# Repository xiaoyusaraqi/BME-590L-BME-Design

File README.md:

# BME-590L-BME-Design
# LED light that is button-activated to switch between the following operating modes:
  Off
  Brightest
  Intermediate Brightness
  Least Bright
  Flashing @ 2 Hz
# Self-contained device with LED and button exposed.
# Extra credit possibilities:
   Battery life indicator
   Waterproof enclosure
   You tell us!
# Constraints
   Run on single battery up to 9 V
   Electronics connected to a single PCB (can be single- or double-sided)
   Cannot weight more than 1 lb
   Cannot have a single dimension > 6 in
   Cannot cost more than $50 to duplicate unit
   Battery must be easily replaceable
# Evaluation

   Minimize weight
   Minimize size
   Maximize Brightest mode
   Minimize power draw / maximize battery life
   Survive 3 foot drop with battery installed
 # Create-and-maintain a GitHub project repository to maintain version history of:
  Mechanical CAD (PDFs + more)
  Electronic CAD (PDFs + more)
  Software
  Testing data
  Design history / notes
  Specification sheets
  Usage notes (README.md)
  Kanban board / Issues / Milestones

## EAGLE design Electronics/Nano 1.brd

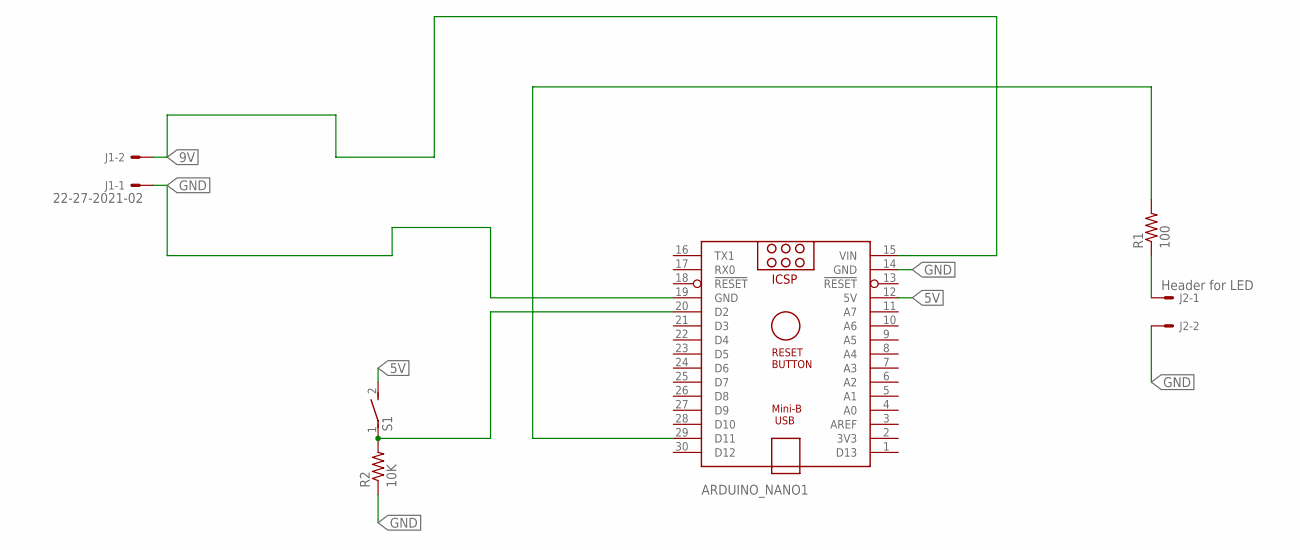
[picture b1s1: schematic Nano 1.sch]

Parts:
ARDUINO_NANO1: ARDUINO_NANO
J1: 22-27-2021-02; 6410-02
J2: Header for LED; 6410-02
R1: 100; 0207/12
R2: 10K; 0207/12
S1: DS01E; DS-01

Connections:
5V: ARDUINO_NANO1.12 (5V), S1.2
9V: ARDUINO_NANO1.15 (VIN), J1.2
+: J2.1, R1.1
GND: ARDUINO_NANO1.14 (GND), ARDUINO_NANO1.19 (GND), J1.1, J2.2, R2.1
unnamed: ARDUINO_NANO1.20 (D2), R2.2, S1.1
unnamed: ARDUINO_NANO1.29 (D11), R1.2

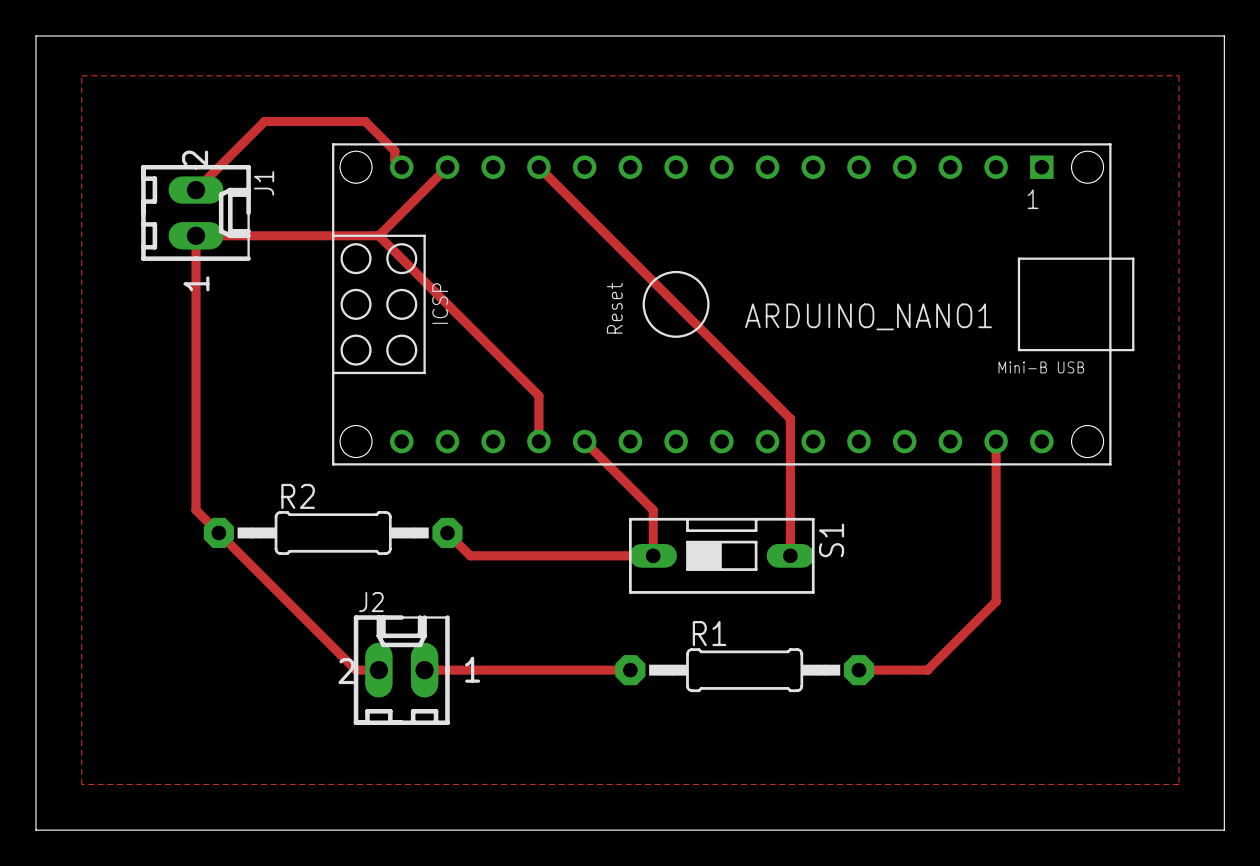
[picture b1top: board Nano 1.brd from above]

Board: 2 copper layers, 66.0 x 44.1 mm, 6 parts (0 on the bottom side), 6 nets.

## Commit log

2018-11-01 Create LED Design Draft
2018-11-09 Create LED SCH&PCB
2018-11-09 Create Data
2018-12-14 Create Software
2018-12-14 Create LED Code
2018-12-14 Create Body of the Box
2018-12-14 Create LId of the Box
2018-12-17 Create Prediction
